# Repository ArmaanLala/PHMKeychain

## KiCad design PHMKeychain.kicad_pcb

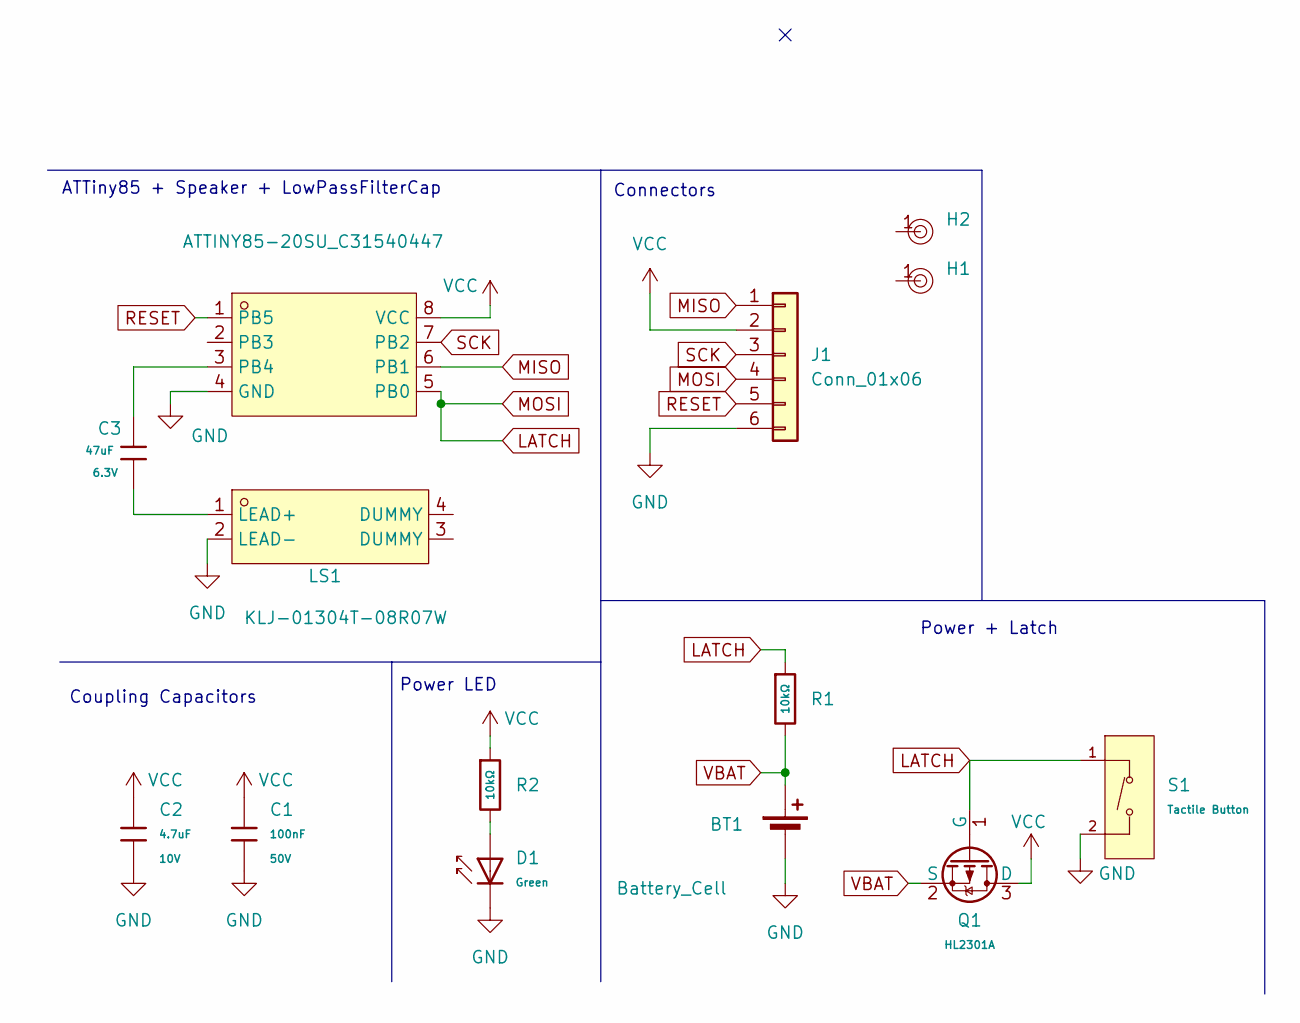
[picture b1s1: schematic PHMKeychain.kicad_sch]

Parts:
BT1: Battery_Cell; BAT-SMD_MY-2032-12
C1: 100nF; C_0603; Voltage Rated 50V; Tolerance ±10%; Part CC0603KRX7R9BB104; LCSC C14663
C2: 4.7uF; C_0402; Voltage Rated 10V; Tolerance ±20%; Part CL05A475MP5NRNC; LCSC C23733
C3: 47uF; C_0805; Voltage Rated 6.3V; Tolerance ±20%; Part CL21A476MQYNNNE; LCSC C16780
D1: Green; D_0805; Part KT-0805G; LCSC C2297
H1, H2: Hole, 3mm
J1: Conn_01x06; PinHeader_1x06_P2.54mm_Vertical
LS1: KLJ-01304T-08R07W; BUZ-SMD_4P-L13.0-W13.0-P11.4-BL; LCSC Part C18186315
Q1: HL2301A; Q_SOT-23; Part HL2301A; LCSC C7420344
R1, R2: 10kΩ; R_0402; Overload Voltage (Max) 50V; Tolerance ±1%; Part 0402WGF1002TCE; LCSC C25744
S1: Tactile Button; SW_TS-1088-AR02016; Voltage Rating (Dc) 12V; Part TS-1088-AR02016; LCSC C720477
U1: ATTINY85-20SU_C31540447; SOIC-8_L5.3-W5.3-P1.27-LS8.0-BL; LCSC Part C31540447

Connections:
GND: BT1.2 (-), C1.2, C2.1, D1.1, J1.6, LS1.2 (LEAD-), S1.2 (B), U1.4 (GND)
LATCH: J1.4, Q1.1 (G), R1.1, S1.1 (A), U1.5 (PB0)
MISO: J1.1, U1.6 (PB1)
unnamed: D1.2, R2.2
unnamed: C3.2, LS1.1 (LEAD+)
unnamed: C3.1, U1.3 (PB4)
RESET: J1.5, U1.1 (PB5)
SCK: J1.3, U1.7 (PB2)
VBAT: BT1.1 (+), Q1.2 (S), R1.2
VCC: C1.1, C2.2, J1.2, Q1.3 (D), R2.1, U1.8 (VCC)

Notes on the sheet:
Power LED
ATTiny85 + Speaker + LowPassFilterCap
Connectors
Coupling Capacitors
Power + Latch

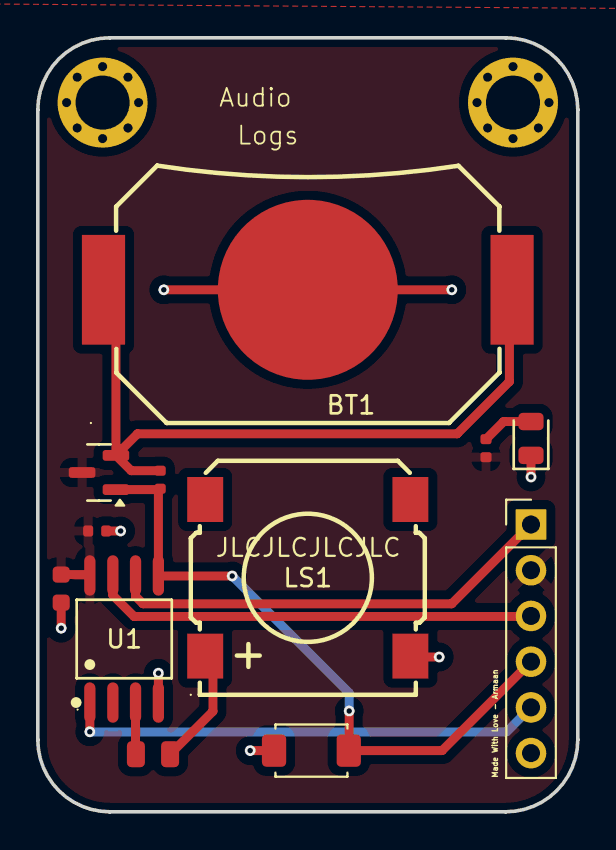
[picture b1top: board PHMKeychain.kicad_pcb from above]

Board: 2 copper layers, 30.0 x 43.0 mm, 14 parts (0 on the bottom side), 10 nets.

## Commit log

2026-03-02 Init Commit
2026-03-02 Organized
2026-03-02 Clean up board
2026-03-03 Added Art
